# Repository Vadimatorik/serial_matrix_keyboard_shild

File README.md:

# serial_matrix_keyboard_shild
Репозиторий содержит исходные данные платы и программного обеспечения универсального контроллера матричной клавиатуры размером до 5x5 элементов.

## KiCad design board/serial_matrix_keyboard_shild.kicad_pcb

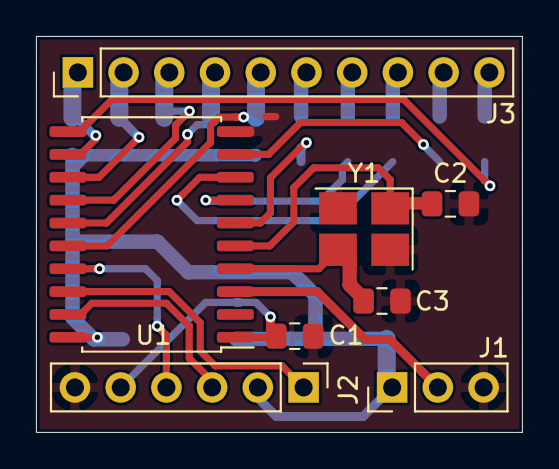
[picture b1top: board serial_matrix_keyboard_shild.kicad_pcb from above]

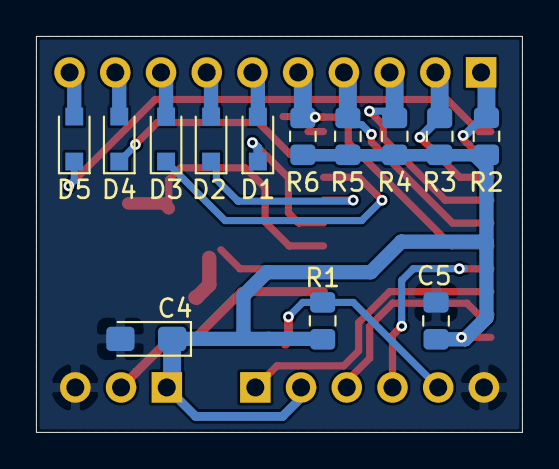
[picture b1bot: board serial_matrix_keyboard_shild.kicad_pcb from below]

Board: 2 copper layers, 27.0 x 22.0 mm, 21 parts (13 on the bottom side), 24 nets.

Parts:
C1, C5: 0.1 мкФ; C_0805_2012Metric_Pad1.15x1.40mm_HandSolder
C2, C3: 22 пФ; C_0805_2012Metric_Pad1.15x1.40mm_HandSolder
C4: 10 мкФ; CP_EIA-3216-18_Kemet-A_Pad1.58x1.35mm_HandSolder
D1, D2, D3, D4, D5: PESD5V0S1BA; D_SOD-323_HandSoldering
J1: DATA; PinHeader_1x03_P2.54mm_Vertical
J2: AVR-ISP-6; PinHeader_1x06_P2.54mm_Vertical
J3: KEYBOARD; PinHeader_1x10_P2.54mm_Vertical
R1, R2, R3, R4, R5, R6: 10 кОм; R_0805_2012Metric_Pad1.15x1.40mm_HandSolder
U1: ATtiny2313-20SU; SOIC-20W_7.5x12.8mm_P1.27mm
Y1: NX3225SA-16.000M-STD-CRS-2; Crystal_SMD_3225-4Pin_3.2x2.5mm_HandSoldering

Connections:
+5V: C4.1, C5.2, J1.1, J2.2, R1.1, R2.2, R3.2, R4.2, R5.2, R6.2, U1.20
/BC0: D1.1, U1.6
/BC1: D2.1, U1.7
/BC2: D3.1, U1.8
/BC3: D4.1, U1.9
/BC4: D5.1, U1.11
/BR0: J3.1, R2.1, U1.12
/BR1: J3.2, R3.1, U1.13
/BR2: J3.3, R4.1, U1.14
/BR3: J3.4, R5.1, U1.15
/BR4: J3.5, R6.1, U1.16
/MISO: J2.1, U1.18
/MOSI: J2.4, U1.17
/RESET: C1.1, J2.5, R1.2, U1.1
/SCK: J2.3, U1.19
/TX: J1.2, U1.3
/XTAL1: C2.1, U1.5, Y1.1
/XTAL2: C3.1, U1.4, Y1.3
GND: C1.2, C2.2, C3.2, C4.2, C5.1, J1.3, J2.6, U1.10, Y1.2, Y1.4
unnamed: D1.2, J3.6
unnamed: D2.2, J3.7
unnamed: D3.2, J3.8
unnamed: D4.2, J3.9
unnamed: D5.2, J3.10

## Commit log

2019-06-18 Нарисована схема и расставлены компоненты.
2019-06-19 Разведена плата.
2019-06-19 Мелкие правки перед производитсвом и добавлены gerber.
2019-06-19 Обновил gerber перед производством. Добавил файлы для сверловки.
2019-06-19 Убрал лишнюю вложенность.
2019-06-19 Поправил gerber (надписи).
2019-06-19 Поправил подпись.
